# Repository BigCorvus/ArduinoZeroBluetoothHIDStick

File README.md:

# ArduinoZeroBluetoothHIDStick

Yet another keystroke injector based on the Arduino Zero/Feather M0 and the HC-05 Bluetooth module

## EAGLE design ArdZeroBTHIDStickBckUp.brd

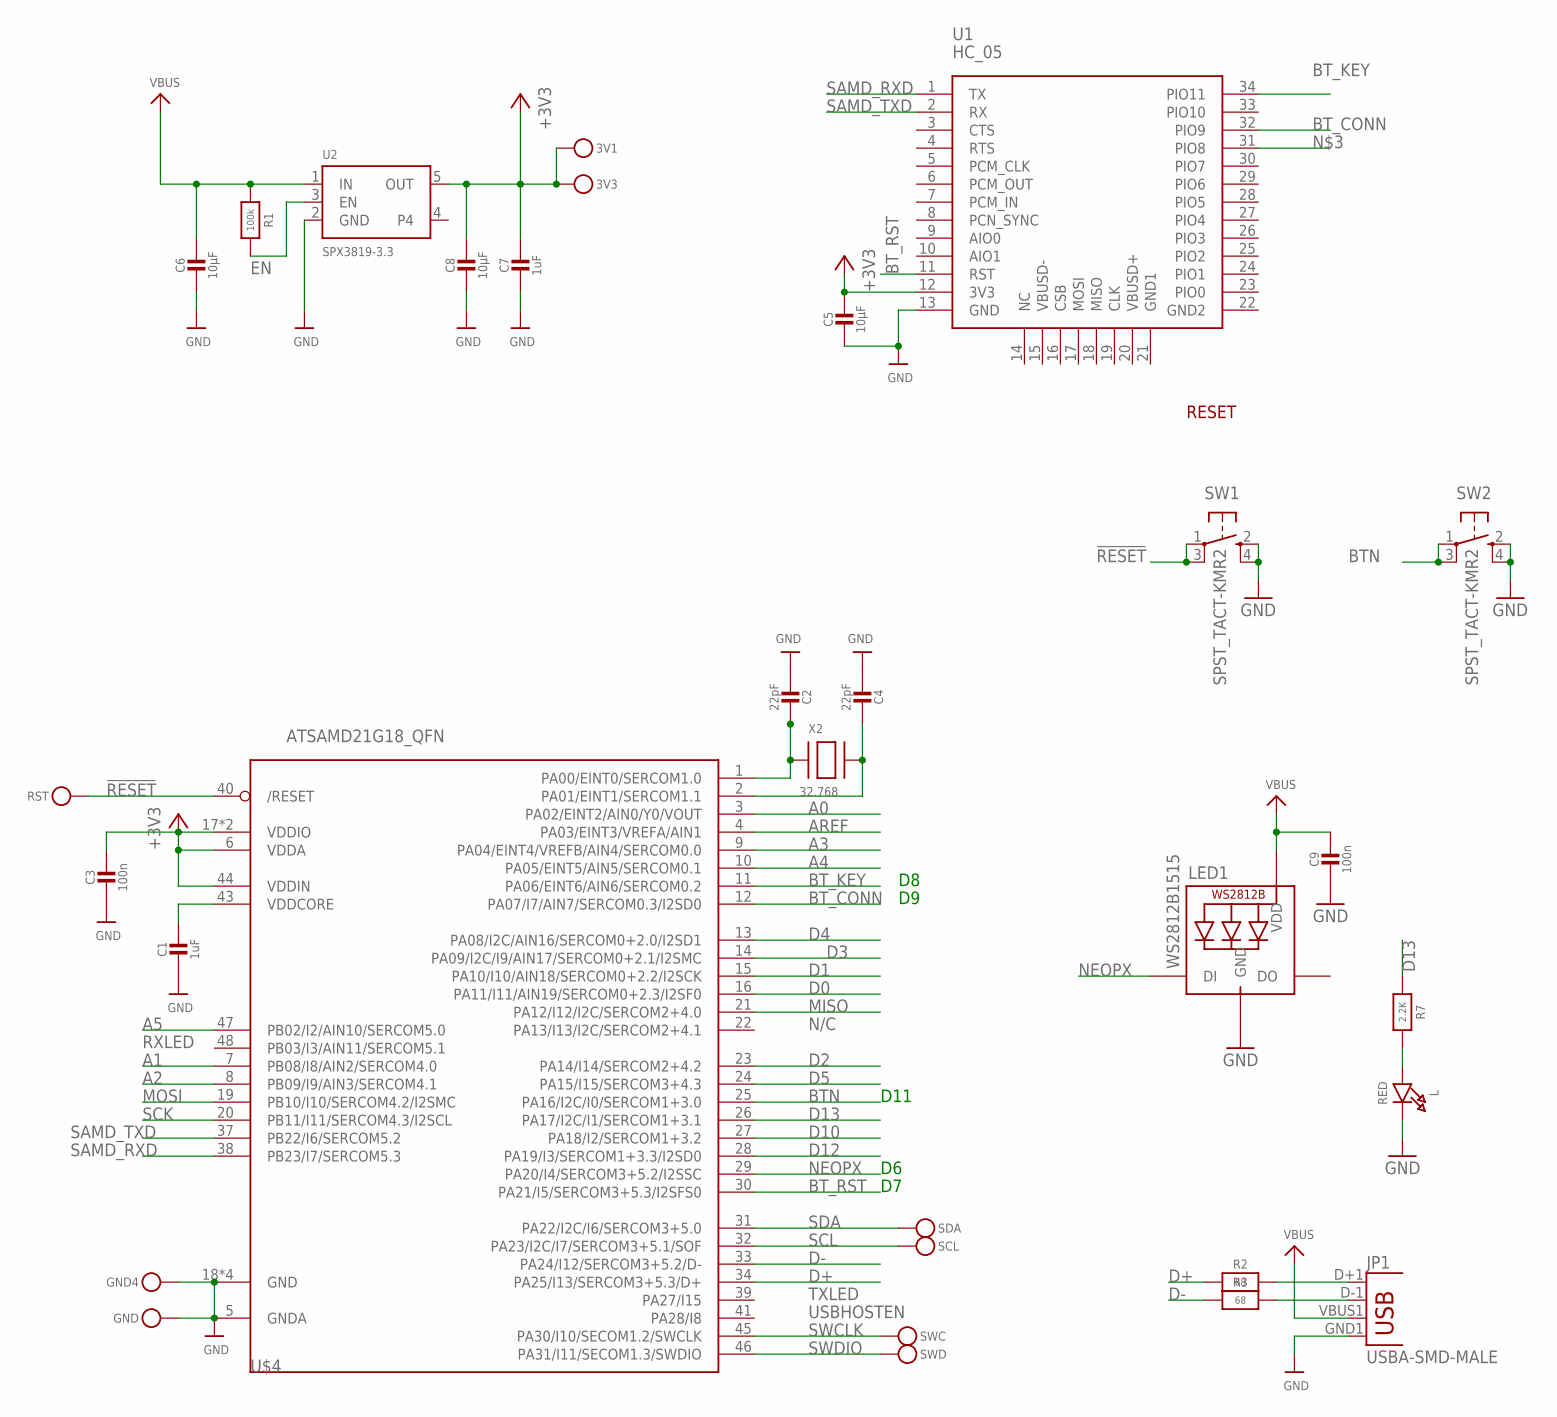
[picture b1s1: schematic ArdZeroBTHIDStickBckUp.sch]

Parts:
3V1, 3V3: TESTPOINTROUND1.5MM; TESTPOINT_ROUND_1.5MM
C1, C7: 1uF; 0603-NO
C2, C4: 22pF; 0603-NO
C3, C9: 100n; 0603-NO
C5, C6, C8: 10µF; 0805-NO
GND, GND4: TESTPOINTROUND1.5MM; TESTPOINT_ROUND_1.5MM
JP1: USBA-SMD-MALE; USB-A-SMT-MALE
L: RED; CHIPLED_0805_NOOUTLINE
LED1: WS2812B1515; LED1515
R1: 100k; 0603-NO
R2, R3: 68; 0603-NO
R7: 2.2K; 0603-NO
RST: TESTPOINTROUND1.5MM; TESTPOINT_ROUND_1.5MM
SCL: TESTPOINTROUND1.5MM; TESTPOINT_ROUND_1.5MM
SDA: TESTPOINTROUND1.5MM; TESTPOINT_ROUND_1.5MM
SW1, SW2: SPST_TACT-KMR2; KMR2
SWC: TESTPOINTROUND1.5MM; TESTPOINT_ROUND_1.5MM
SWD: TESTPOINTROUND1.5MM; TESTPOINT_ROUND_1.5MM
U1: HC_05; BLUETOOTH_SMD
U2: SPX3819-3.3; SOT23-5
U$4: ATSAMD21G18_QFN; TQFN48_7MM
X2: 32.768; XTAL3215

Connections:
!RESET: RST.P$1, SW1.1, SW1.3 (P1), U$4.40 (/RESET)
+3V3: 3V1.P$1, 3V3.P$1, C3.1, C5.1, C7.1, C8.1, U1.12 (3V3), U2.5 (OUT), U$4.6 (VDDA), U$4.17 (VDDIO), U$4.36 (VDDIO), U$4.44 (VDDIN)
A0: U$4.3 (PA02/EINT2/AIN0/Y0/VOUT)
A1: U$4.7 (PB08/I8/AIN2/SERCOM4.0)
A2: U$4.8 (PB09/I9/AIN3/SERCOM4.1)
A3: U$4.9 (PA04/EINT4/VREFB/AIN4/SERCOM0.0)
A4: U$4.10 (PA05/EINT5/AIN5/SERCOM0.1)
A5: U$4.47 (PB02/I2/AIN10/SERCOM5.0)
AREF: U$4.4 (PA03/EINT3/VREFA/AIN1)
BTN: SW2.1, SW2.3 (P1), U$4.25 (PA16/I2C/I0/SERCOM1+3.0)
BT_CONN: U1.32 (PIO9), U$4.12 (PA07/I7/AIN7/SERCOM0.3/I2SD0)
BT_KEY: U1.34 (PIO11), U$4.11 (PA06/EINT6/AIN6/SERCOM0.2)
BT_RST: U1.11 (RST), U$4.30 (PA21/I5/SERCOM3+5.3/I2SFS0)
D0: U$4.16 (PA11/I11/AIN19/SERCOM0+2.3/I2SF0)
D1: U$4.15 (PA10/I10/AIN18/SERCOM0+2.2/I2SCK)
D2: U$4.23 (PA14/I14/SERCOM2+4.2)
D3: U$4.14 (PA09/I2C/I9/AIN17/SERCOM0+2.1/I2SMC)
D4: U$4.13 (PA08/I2C/AIN16/SERCOM0+2.0/I2SD1)
D5: U$4.24 (PA15/I15/SERCOM3+4.3)
D10: U$4.27 (PA18/I2/SERCOM1+3.2)
D12: U$4.28 (PA19/I3/SERCOM1+3.3/I2SD0)
D13: R7.1, U$4.26 (PA17/I2C/I1/SERCOM1+3.1)
D+: R2.1, U$4.34 (PA25/I13/SERCOM3+5.3/D+)
D-: R3.1, U$4.33 (PA24/I12/SERCOM3+5.2/D-)
EN: R1.2, U2.3 (EN)
GND: C1.2, C2.2, C3.2, C4.2, C5.2, C6.2, C7.2, C8.2, C9.2, GND.P$1, GND4.P$1, JP1.GND1 (GND), L.C, LED1.GND, SW1.2 (S), SW1.4 (S1), SW2.2 (S), SW2.4 (S1), U1.13 (GND), U2.2 (GND), U$4.5 (GNDA), U$4.18 (GND), U$4.35 (GND), U$4.42 (GND), U$4.THERMAL (GND)
MISO: U$4.21 (PA12/I12/I2C/SERCOM2+4.0)
MOSI: U$4.19 (PB10/I10/SERCOM4.2/I2SMC)
unnamed: JP1.D+1 (D+), R2.2
unnamed: JP1.D-1 (D-), R3.2
unnamed: C2.1, U$4.1 (PA00/EINT0/SERCOM1.0), X2.P$1
unnamed: L.A, R7.2
unnamed: C4.1, U$4.2 (PA01/EINT1/SERCOM1.1), X2.P$2
NEOPX: LED1.DIN (DI), U$4.29 (PA20/I4/SERCOM3+5.2/I2SSC)
SAMD_RXD: U1.1 (TX), U$4.38 (PB23/I7/SERCOM5.3)
SAMD_TXD: U1.2 (RX), U$4.37 (PB22/I6/SERCOM5.2)
SCK: U$4.20 (PB11/I11/SERCOM4.3/I2SCL)
SCL: SCL.P$1, U$4.32 (PA23/I2C/I7/SERCOM3+5.1/SOF)
SDA: SDA.P$1, U$4.31 (PA22/I2C/I6/SERCOM3+5.0)
SWCLK: SWC.P$1, U$4.45 (PA30/I10/SECOM1.2/SWCLK)
SWDIO: SWD.P$1, U$4.46 (PA31/I11/SECOM1.3/SWDIO)
VBUS: C6.1, C9.1, JP1.VBUS1 (VBUS), LED1.VDD, R1.1, U2.1 (IN)
VDDCORE1: C1.1, U$4.43 (VDDCORE)

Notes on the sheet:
N/C
TXLED
USBHOSTEN
RXLED
RESET
D11

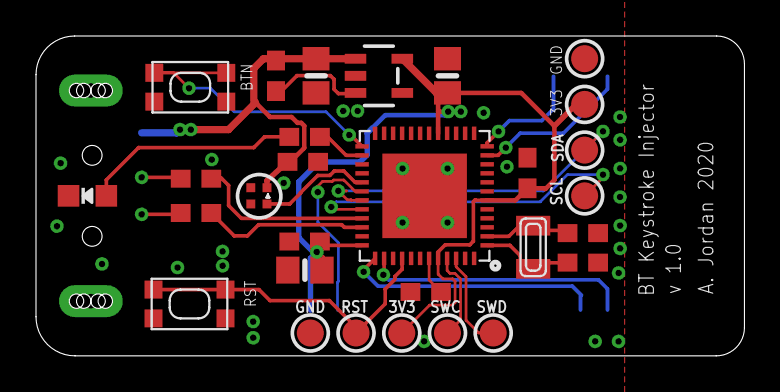
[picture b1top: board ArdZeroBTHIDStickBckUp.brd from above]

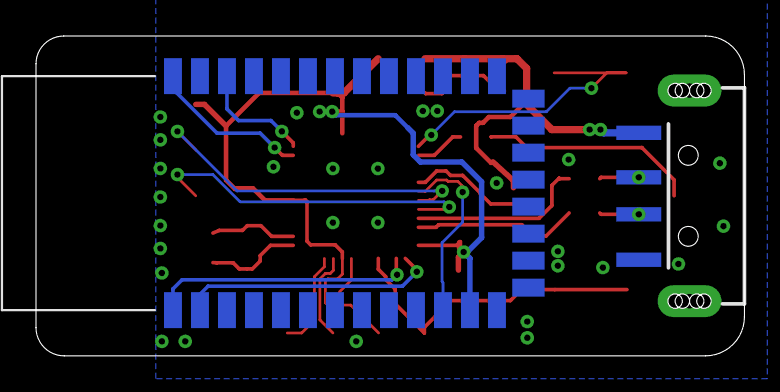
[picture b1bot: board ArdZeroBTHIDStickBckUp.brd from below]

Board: 2 copper layers, 39.4 x 17.8 mm, 31 parts (2 on the bottom side), 25 nets.

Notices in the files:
parts and their libraries:
SparkFun-Connectors: Licensing: Creative Commons ShareAlike 4.0 International - https://creativecommons.org/licenses/by-sa/4.0
microbuilder: This work is placed in the public domain, and may be freely used for commercial and non-commercial work with the following conditions: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
